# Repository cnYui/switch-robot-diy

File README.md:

# 86 开关机器人与 Wi-Fi 遥控桥接器：V0.1 设计草稿

## 用自己的电脑当家庭中枢（2026-11-14）

开关（V0.5 板，ESP32-C3）通过家里 Wi-Fi 直连电脑，不需要单独的网关板：电脑上的 HomeHub 带一个 Mosquitto，把所有消息存进电脑里的 SQLite，提供局域网控制页面和手机快捷指令接口，电脑自带蓝牙顺便收体重秤广播。三部分：

- `hub/`：电脑端中枢，安装和使用见 hub/README.md，消息格式见 hub/PROTOCOL.md。
- `firmware/switch_mqtt/`：开关固件，release/ 里有可以直接用 esptool 烧的镜像。
- `enclosure/`：控制盒 V0.4，在 V0.3 盒上补了对准 V0.5 USB-C 的开口。

固件还没在实物板上跑过；中枢用模拟开关和真实 Mosquitto 跑通过整条链路。

## 仓库说明

内容：Blender 机械件（mechanical/、fit-check/、demo/）、嘉立创 EDA 控制板（electronics/）、MuJoCo 仿真（simulation/）。全部是仿真与设计稿，没有实物验证，不能直接投产。

没有放进仓库的：`tools/`（嘉立创官方桥接 [easyeda-api-skill](https://github.com/easyeda/easyeda-api-skill)、freerouting 布线器 jar、本机 MCP 虚拟环境）、`simulation/.venv`（按 simulation/requirements.txt 重新安装）、`demo/frames` 和 `demo/captioned_frames`（演示视频的逐帧图）、日志和一个过期的打包 zip。仿真脚本要在 simulation 目录里直接用虚拟环境的 python 运行，Blender 脚本用 `blender -b --python xxx.py`。文档里的 `C:/Users/yui/...` 之类路径是作者本机路径。本仓库暂未指定许可证。

此目录包含通过本机 Blender MCP 和嘉立创官方 API Gateway 创建的机械原型与电路布局草稿。日期：2026-11-05。

## V0.6 机械修复（2026-11-12，仅仿真验证）

MuJoCo 仿真发现的机械问题已经按下面修改，细节和数据见 simulation/README.md：

- 按压臂换成 V0.6：mechanical/PRINT_03_double_press_arm.stl（已按“棒材平放、指杆朝上”的打印朝向导出，0 个非流形边）。旧版归档在 mechanical/archive，文件名带 DO_NOT_PRINT。Blender 装配在 mechanical/switch_robot_86_v06.blend，由 mechanical/build_v06.py 生成；switch_robot_86_v01.blend 没有改动。
- 指杆下端抬高到 17.5 mm，下面粘两块 4×7×5.5 mm 的弹性压垫（泡棉或 TPU，外购，不在 STL 内）。
- 支架整体垫高 1.0 mm：每个安装脚下叠两片 0.5 mm 的 M3 平垫圈，增减 0.5 mm 即可微调安装高度。
- 舵机名义按压角改为 17°。固件还没有写，这个角度只是仿真里的数值。
- 框 PRINT_01 把 (42, ±29) 的 3.4 mm 通槽改成 Ø2.5 mm 预钻孔（槽下面是 86 面板，钉头放不下）。螺丝、垫圈、扎带、压垫等采购规格见 mechanical/HARDWARE_BOM.md。
- 回位弹簧（0.05 N·m/rad 以上）仿真里有效，但还没有进 CAD；没有它，断电后臂会停在压垫刚脱离翘板的位置。

没有解决的：翻转阻力 5 N 以上的开关会把压垫压到底，9 N 的开关舵机推不动，只能量到真实开关力之后选舵机。压垫刚度、行程、开关力和舵机反向转动阻力全是假设值，需要实物测量。electronics/ 没有改动，本次修改不影响 PCB。下面的内容是 V0.1 的原始说明。

## 当前状态

机械：已保存 Blender 原生工程和五个毫米单位 STL，五个零件的网格检查均为 0 个非流形边。网格闭合不代表已经通过装配、运动干涉、强度和真实开关的按压力测试。尚未实际打印。

电路：在嘉立创中创建了独立本地工程，完成 60×40 mm 板框、四个 M3 安装孔、40 个有网络的电气焊盘、接口与器件的初步摆放和部分布线。当前使用独立焊盘与丝印描述封装，尚未注册为完整器件库元件。概念接线图使用图形块及导线，并不是完成 ERC 检查、能与 PCB 自动同步的电气原理图。不能据此直接打样或生成装配订单。

嘉立创 DRC 已执行并修复发现的 +5V 走线间距冲突；最后一次检查仍有 Connection Error，来自未完成的网络连接。完整结果见 electronics/drc_draft.json。不存在“DRC 已通过”的结论。

电脑连接的 Espressif Device / COM8 尚未识别出具体芯片型号。本稿没有假定它的 GPIO 引脚、外形尺寸或 Wi-Fi/蓝牙能力，也没有改动它的固件。

## 两种使用路线

自制机器人：经确认支持联网的 ESP32 通过网络服务接收命令，由 PWM 控制舵机，双向按压臂分别压下翘板开关两端。第一版以 SG90 类成品舵机的约 23×12.2×29 mm 包络作尺寸参考，没有设计舵机内部的电机、反馈电位器、齿轮或控制器。

现成机器人改造：保留原遥控器与电池，把板上 J4 或 J5 的两根隔离输出线并接在原遥控器相应按键的两个电气节点上。ESP32 触发 PhotoMOS，让原遥控器发送原有无线指令。需要先测量按键电压、接触方式、导通电阻要求、漏电容忍度；触摸式按键或特殊扫描电路可能不适用。无需假定其无线方式是红外、315/433 MHz 射频还是其他协议。

PhotoMOS 只针对低压遥控器按键，本 PCB 未按市电隔离规范设计。J4/J5 不与本板 GND 相连。板上接口不提供灯已实际开/关的状态检测；只有一个切换按键的遥控器也不能保证命令等价于独立 ON/OFF。

异地控制还需要远程服务：例如 MQTT 服务器，或 Home Assistant 加远程访问。ESP32 本身接上家庭 Wi-Fi 只解决局域网连接。本稿没有部署服务器、写入 Wi-Fi 凭据、实现米家接入或实现可用的远程控制固件。

## 机械文件

mechanical/switch_robot_86_v01.blend 是原生装配场景；assembly_preview.png 是 Blender 渲染。五个 PRINT_*.stl 是独立结构零件，导出单位为 mm。蓝色舵机、绿色 PCB 和开关面板是包络参考，不是打印件。

安装框外尺寸 96×96 mm、内开口 72×72 mm、厚度 3 mm。内侧落在 86 面板边缘附近；实际使用前需要核对原面板边缘可粘贴区域和摇板活动范围。四边并未为所有多联面板保证兼容。

托架采用绑带固定舵机，滑槽允许调整相对位置。双臂半跨度 24 mm，压脚中心位于两端；舵机轴线参考高度 25 mm。使用舵机原装舵盘作转接，中心孔和两侧孔只是原型孔位，必须按实际舵盘复核，不包含可直接咬合舵机花键的精密齿形。先干装并检查中立位置两端都脱离开关，再逐步校准两侧行程，8° 只是最初的几何参考，不是可直接使用的固件控制角度。

（V0.7 起网关盒换成 76×56×30 mm 的 V0.3 版，下面 68×48×22 的旧盒四根盖柱会顶住 PCB 四角，已移到 mechanical/archive。）网关盒外尺寸 68×48×22 mm，壁厚约 2 mm，适配 60×40 mm PCB。PCB 孔位为 (4,4)、(56,4)、(56,36)、(4,36) mm。壳体螺柱按小螺钉自攻试孔设计，实际螺钉与打印收缩需要校核。主控包络仅为占位，不能当作电脑所连板子的尺寸。电容、接插件与实际主控的高度都未完成包络复核。

STL 导出只是平移到底面，未给所有零件选择最佳打印朝向。特别是托架与双臂，应在切片软件中旋转并检查悬垂、孔位和支撑；不能把“平底导出”理解为“全部免支撑”。建议先用低成本材料做尺寸样件，再决定最终材料、壁厚和填充。

## 电路接口与初选器件

J1：1=5V 输入，2=GND。F1 暂为 5.08 mm 间距的自恢复保险丝占位，保持电流、动作电流和压降需要根据实测舵机启动/堵转电流选择。没有输入反接保护和电源管理。

J2：1=GND，2=PWM，3=KEY1，4=KEY2，5=AUX。使用来自已确认主控的 3.3V GPIO；GPIO 选择避开启动绑带、USB 和板上已有功能。主控暂由自己的 USB 供电，与 J1 共地，不把外部 5V 倒灌到未知开发板。

J3：1=GND，2=+5V，3=SERVO。连接前核对舵机线序与 3.3V PWM 兼容性。舵机使用独立充足的 5V 电源，不能从 ESP32 的 3.3V 引脚供电。C1 初选 470uF/10V、5 mm 脚距；C2 为 100nF、2.54 mm 脚距，实际封装均需核对。

U1/U2 初选 Panasonic AQY212EH DIP4 PhotoMOS：1=输入 LED 阳极，2=输入 LED 阴极，3/4=隔离开关输出。布局采用 7.62 mm 跨距、2.54 mm 引脚间距的初步孔位，投板前仍要按采购料号尺寸图核对。R1/R2 为 470Ω，配合 3.3V GPIO 驱动；R3/R4 为 100kΩ 下拉。R5 为 220Ω PWM 串联电阻，R6 为 100kΩ PWM 下拉。电阻孔距均为 7.62 mm 的手焊原型占位。

J4：BTN1_A / BTN1_B；J5：BTN2_A / BTN2_B。分别跨接到遥控器对应按键，隔离输出没有正负极方向约束，但能否正确触发仍要实测。控制程序应使用短脉冲并在开机默认保持输出关闭；固件尚未编写。

## 可编辑源与复现

design_parameters.json 保存初始尺寸。model_robot.py 为常规 Blender Python 源，model_robot_mcp.py 为适用于当前 MCP 安全模式的自包含脚本。已有 Blender 场景经过额外的 2 mm 按压臂侧向间隙修正，两份脚本也已同步该修正。

create_pcb_draft.js、create_wiring_concept.js 保存编辑器调用源；eda_client.py 调用本机官方桥接器。它们是生成脚本，重跑会追加图元，不应在已有文档直接重复运行。电路后续进行过一次定点间距修正，已同步到 create_pcb_draft.js；布局元数据 placement_and_nets.json 记录的是初始放置，最终几何以 carrier_v01.epcb 和原生工程为准。PCB 脚本假设先创建了单一闭合板框。

electronics/native-project 保存完整嘉立创本地工程快照，使用其中 .eprj3 工程打开。原编辑器工程保存在 C:/Users/yui/Documents/LCEDA-Pro/projects/Switch Robot DIY V0.1。electronics 下同时保留 .epcb、.esch 源文档与接线 SVG。

tools/easyeda-api-skill 为本次使用的官方桥接依赖本地副本，不是产品固件。start_blender_mcp.py 用于启动已安装的 Blender MCP 插件。

## 下一步需要的实物验证

识别主控型号与可用 GPIO；测量具体舵机及舵盘；测量摇板宽高、转轴位置、按压行程及力；确认遥控器按键电压与触点。完成这些后，再选择自制机械臂或改造遥控器的实际路线，补完整器件库与电气原理图、完成布线和 ERC/DRC，通过台架测试后才具备打样依据。

## 参考

SG90 原厂尺寸：https://torqpro.com/product/sg90-analog/

PhotoMOS 原厂资料：https://na.industrial.panasonic.com/products/relays-contactors/semiconductor-relays/lineup/photomos-relays/series/12428

ESPHome 红外/射频转发：https://esphome.io/components/remote_transmitter/

米家产品接入：https://iot.mi.com/new/doc/accesses/direct-access/productcenter/create-product

嘉立创官方桥接：https://github.com/easyeda/easyeda-api-skill

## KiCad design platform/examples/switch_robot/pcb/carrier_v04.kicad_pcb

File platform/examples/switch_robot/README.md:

开关机器人示例：本仓库的 86 开关按压机器人，机械模型直接复用 simulation/model.py（scripts/export_mjcf.py 导出成 mechanics/switch_robot.xml，网格引用 simulation/assets，不复制），PCB 是 electronics/v04 的控制板（pcb/carrier_v04.kicad_pcb，由 EasyEDA Pro 源文件转换），固件是 platform/firmware/switch_robot。

project.yaml 由 build_example.py 生成，步骤和 AI 通过 MCP 做的一样：import_pcb → import_model → import_firmware → define_joint（servo_axis、rocker_axis）→ 电源网络（C1+C2 的 470.1 µF 和 J1→F1→J3 的铜皮电阻取自 PCB）→ bind_pin（GPIO18 经 J2.2/PWM_IN、R5 到 J3.3 舵机信号；GPIO0 接按键）。翘板的双稳态弹簧（3 N 峰值、±3.5°）原来在 model.py 的 Python 代码里，这里成了 project.yaml 的 rocker_detent 元素。

工程里舵机的供电写的是“台架接法”：舵机红线接在开发板的 5V 引脚上，和 ESP32 共用电脑 USB 口（500 mA 限流）。PCB 的设计是舵机从 J3 取电、经 F1 由 J1 外接 5 V 供电，ESP32 另行供电。这样写是为了复现故障，修复就是把 actuators.servo1.node 改成 v5_servo。

三个场景：toggle_nominal 按两次键，3 N 开关先开后关，全部断言通过；stall_brownout 换成 9 N 硬开关，舵机堵转把 USB 口拉进限流，5 V 掉到 1 V 左右，LDO 输出跌到 2.1 V，ESP32 以 BROWNOUT 原因重启；servo_sweep_scripted 不跑固件，直接给 GPIO18 脉宽，用来快速检查机电链路。

DEMO.md 是 scripts/demo_ai_loop.py 通过 MCP 跑出来的完整记录：先复现故障，再扫固件按压角（13° 在两种开关下都过了，但离限流只差约 14 mA，不可信），再扫舵机供电接法，最后 set_param 把舵机改接 J3 并重测。改完后 ESP32 不再重启，正常开关照常工作；9 N 开关仍然推不动，和 simulation/README.md 的结论一致。

所有电机、电源、开关参数都是假设值，标注在 project.yaml 的 note 里。

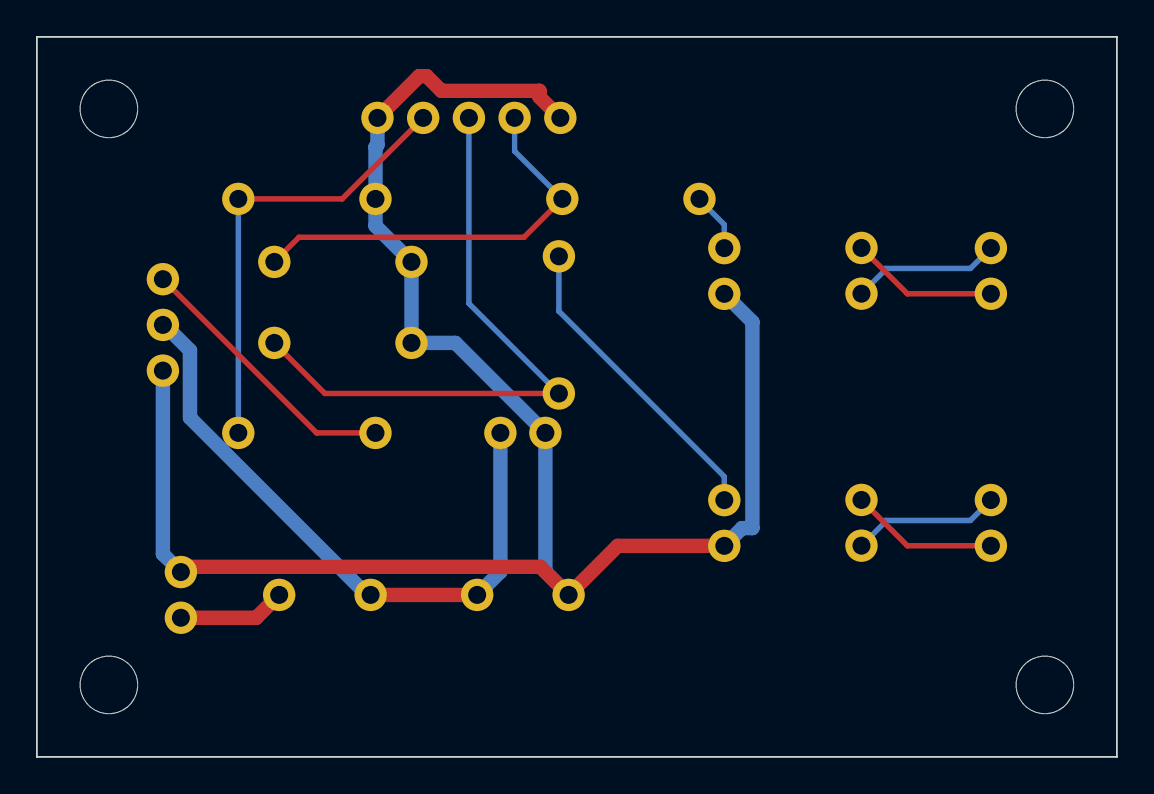
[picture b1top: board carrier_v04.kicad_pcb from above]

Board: 2 copper layers, 60.0 x 40.0 mm, 20 parts (0 on the bottom side), 13 nets.

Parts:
C1: 470uF; CAP-TH_BD10.0-P5.00-D1.0-FD
C2: 100nF; CAP-TH_L4.0-W2.5-P2.50-D0.5
F1: RUEF110; FUSE-TH_L7.0-W3.1-P5.08-D1.2
H1, H2, H3, H4: MountingHole; NPTH
J1, J4, J5: PZ254V-11-02P; HDR-TH_2P-P2.54-V-M
J2: PZ254V-11-05P; HDR-TH_5P-P2.54-V-M
J3: PZ254V-11-03P; HDR-TH_3P-P2.54-V-M_PZ254V-11-03P
R1, R2: 470Ω; RES-TH_BD2.3-L3.7-P7.70-D0.9
R3, R4, R6: 100kΩ; RES-TH_BD2.3-L3.7-P7.70-D0.9
R5: 220Ω; RES-TH_BD2.3-L3.7-P7.70-D0.9
U1, U2: AQY212EH; DIP-4_L6.4-W4.8-P2.54-LS7.6-BL

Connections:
BTN1_A: J4.1, U1.4
BTN1_B: J4.2, U1.3
BTN2_A: J5.1, U2.4
BTN2_B: J5.2, U2.3
GND: C1.2, C2.2, J1.2, J2.1, J2.5, J3.1, R3.2, R4.2, R6.2, U1.2, U2.2
KEY1: J2.3, R1.1, R3.1
KEY2: J2.4, R2.1, R4.1
LED1: R1.2, U1.1
LED2: R2.2, U2.1
PWM_IN: J2.2, R5.1, R6.1
SERVO_SIG: J3.3, R5.2
V5_SERVO: C1.1, C2.1, F1.2, J3.2
VIN5: F1.1, J1.1

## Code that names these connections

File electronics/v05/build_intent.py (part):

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        'copper_oz': 1,
        'mount_holes_mm': [[4, 4, 3.2], [56, 4, 3.2], [56, 36, 3.2], [4, 36, 3.2]],
        'description': 'ESP32-C3-MINI-1-N4 integrated carrier: one 5V positional servo and two isolated remote-button outputs, USB-C power/programming. Does not switch mains.',
        'gpio': {'GPIO4': 'PWM_IN', 'GPIO5': 'KEY1', 'GPIO6': 'KEY2', 'GPIO9': 'BOOT', 'GPIO18': 'USB_DN', 'GPIO19': 'USB_DP',
                 'GPIO20': 'UART_RX', 'GPIO21': 'UART_TX', 'GPIO2': 'IO2_STRAP (10k pull-up)', 'GPIO8': 'IO8_STRAP (10k pull-up)', 'EN': 'EN'},
        'parts': parts,
    }
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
